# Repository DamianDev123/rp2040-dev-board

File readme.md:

# My RP2040 Dev Board

A simple RP2040 development board designed to help me learn PCB design and gain experience creating custom hardware.

## Features
- RP2040 microcontroller
- USB-C for power and programming
- BOOT and RESET buttons
- Status LED
- Broken out GPIO pins
- SWD debugging header
- Designed in KiCad

## Renders

### Front

### Back

## Project Structure

```
PCB/         - KiCad project files
Renders/     - PCB renders
Fabrication/ - Final Stuff
CAD/         - Just an export of the PCB
```

## Goals

This project was made to:
- Learn the PCB design workflow
- Practice schematic capture and PCB layout
- Understand RP2040 hardware design
- Gain experience preparing boards for manufacturing

## Software

Designed using **KiCad**.

## License

This project is open source under the MIT License.

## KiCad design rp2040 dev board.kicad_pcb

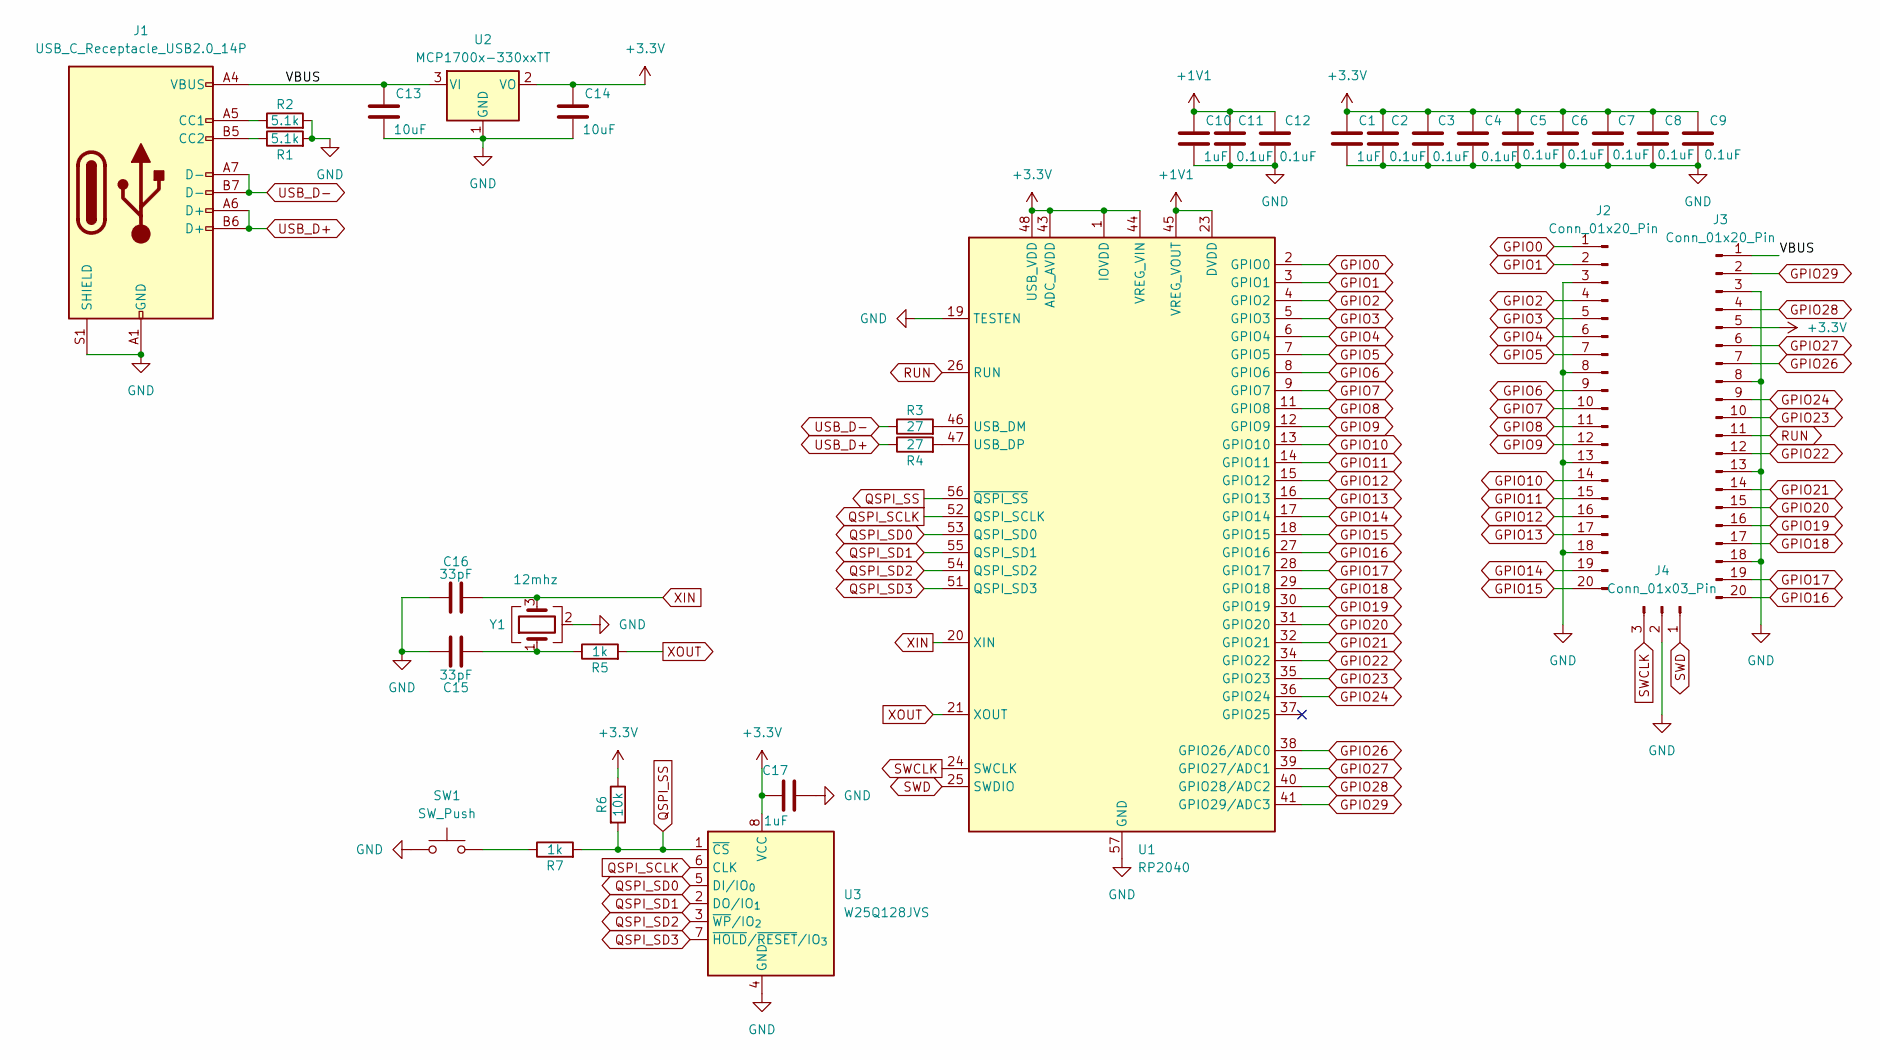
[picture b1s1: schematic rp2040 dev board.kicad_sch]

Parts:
C1, C10, C17: 1uF; C_0402_1005Metric
C2, C3, C4, C5, C6, C7, C8, C9, C11, C12: 0.1uF; C_0402_1005Metric
C13, C14: 10uF; C_0603_1608Metric
C15, C16: 33pF; C_0402_1005Metric
J1: USB_C_Receptacle_USB2.0_14P; USB_C_Receptacle_HRO_TYPE-C-31-M-12
J2, J3: Conn_01x20_Pin; PinHeader_1x20_P2.54mm_Vertical
J4: Conn_01x03_Pin; PinHeader_1x03_P2.54mm_Vertical
R1, R2: 5.1k; R_0402_1005Metric
R3, R4: 27; R_0402_1005Metric
R5, R7: 1k; R_0402_1005Metric
R6: 10k; R_0402_1005Metric
SW1: SW_Push; SW_Push_SPST_NO_Alps_SKRK
U1: RP2040; QFN-56-1EP_7x7mm_P0.4mm_EP3.2x3.2mm
U2: MCP1700x-330xxTT; SOT-23
U3: W25Q128JVS; Winbond_USON-8-1EP_3x2mm_P0.5mm_EP0.2x1.6mm
Y1: 12mhz; Crystal_SMD_3225-4Pin_3.2x2.5mm

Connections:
+1V1: C10.1, C11.1, C12.1, U1.23 (DVDD), U1.45 (VREG_VOUT), U1.50 (DVDD)
+3.3V: C1.1, C2.1, C3.1, C4.1, C5.1, C6.1, C7.1, C8.1, C9.1, C14.1, C17.1, J3.5, R6.1, U1.1 (IOVDD), U1.10 (IOVDD), U1.22 (IOVDD), U1.33 (IOVDD), U1.42 (IOVDD), U1.43 (ADC_AVDD), U1.44 (VREG_VIN), U1.48 (USB_VDD), U1.49 (IOVDD), U2.2 (VO), U3.8 (VCC)
/VBUS: C13.1, J1.A4 (VBUS), J1.A9 (VBUS), J1.B4 (VBUS), J1.B9 (VBUS), J3.1, U2.3 (VI)
GND: C1.2, C2.2, C3.2, C4.2, C5.2, C6.2, C7.2, C8.2, C9.2, C10.2, C11.2, C12.2, C13.2, C14.2, C15.1, C16.1, C17.2, J1.A1 (GND), J1.A12 (GND), J1.B1 (GND), J1.B12 (GND), J1.S1 (SHIELD), J2.3, J2.8, J2.13, J2.18, J3.3, J3.8, J3.13, J3.18, J4.2, R1.2, R2.2, SW1.1, U1.19 (TESTEN), U1.57 (GND), U2.1 (GND), U3.4 (GND), Y1.2 (G), Y1.4 (G)
GPIO0: J2.1, U1.2 (GPIO0)
GPIO1: J2.2, U1.3 (GPIO1)
GPIO2: J2.4, U1.4 (GPIO2)
GPIO3: J2.5, U1.5 (GPIO3)
GPIO4: J2.6, U1.6 (GPIO4)
GPIO5: J2.7, U1.7 (GPIO5)
GPIO6: J2.9, U1.8 (GPIO6)
GPIO7: J2.10, U1.9 (GPIO7)
GPIO8: J2.11, U1.11 (GPIO8)
GPIO9: J2.12, U1.12 (GPIO9)
GPIO10: J2.14, U1.13 (GPIO10)
GPIO11: J2.15, U1.14 (GPIO11)
GPIO12: J2.16, U1.15 (GPIO12)
GPIO13: J2.17, U1.16 (GPIO13)
GPIO14: J2.19, U1.17 (GPIO14)
GPIO15: J2.20, U1.18 (GPIO15)
GPIO16: J3.20, U1.27 (GPIO16)
GPIO17: J3.19, U1.28 (GPIO17)
GPIO18: J3.17, U1.29 (GPIO18)
GPIO19: J3.16, U1.30 (GPIO19)
GPIO20: J3.15, U1.31 (GPIO20)
GPIO21: J3.14, U1.32 (GPIO21)
GPIO22: J3.12, U1.34 (GPIO22)
GPIO23: J3.10, U1.35 (GPIO23)
GPIO24: J3.9, U1.36 (GPIO24)
GPIO26: J3.7, U1.38 (GPIO26/ADC0)
GPIO27: J3.6, U1.39 (GPIO27/ADC1)
GPIO28: J3.4, U1.40 (GPIO28/ADC2)
GPIO29: J3.2, U1.41 (GPIO29/ADC3)
unnamed: C15.2, R5.1, Y1.1
unnamed: J1.A5 (CC1), R2.1
unnamed: J1.B5 (CC2), R1.1
unnamed: R7.1, SW1.2
unnamed: R3.2, U1.46 (USB_DM)
unnamed: R4.2, U1.47 (USB_DP)
QSPI_SCLK: U1.52 (QSPI_SCLK), U3.6 (CLK)
QSPI_SD0: U1.53 (QSPI_SD0), U3.5 (DI/IO_{0})
QSPI_SD1: U1.55 (QSPI_SD1), U3.2 (DO/IO_{1})
QSPI_SD2: U1.54 (QSPI_SD2), U3.3 (~WP/IO_{2})
QSPI_SD3: U1.51 (QSPI_SD3), U3.7 (~HOLD/~RESET/IO_{3})
QSPI_SS: R6.2, R7.2, U1.56 (~QSPI_SS), U3.1 (~CS)
RUN: J3.11, U1.26 (RUN)
SWCLK: J4.3, U1.24 (SWCLK)
SWD: J4.1, U1.25 (SWDIO)
USB_D+: J1.A6 (D+), J1.B6 (D+), R4.1
USB_D-: J1.A7 (D-), J1.B7 (D-), R3.1
XIN: C16.2, U1.20 (XIN), Y1.3
XOUT: R5.2, U1.21 (XOUT)

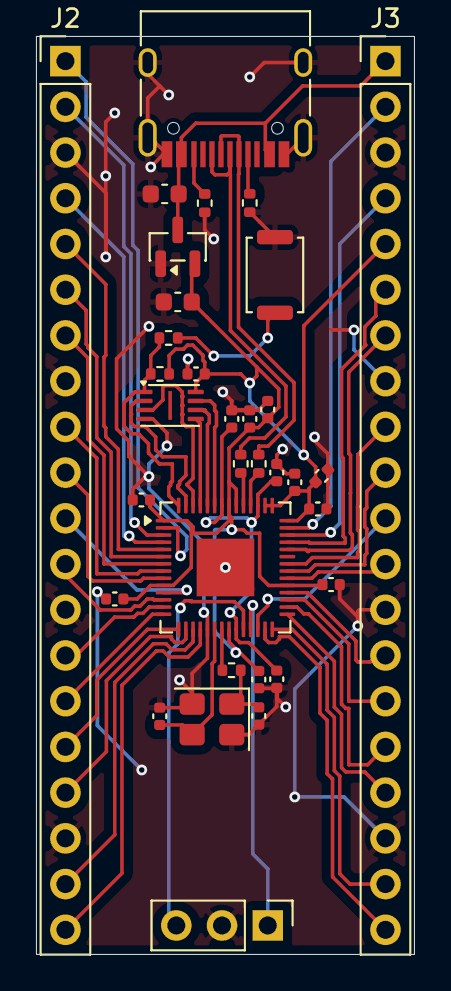
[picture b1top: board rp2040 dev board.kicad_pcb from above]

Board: 2 copper layers, 21.0 x 51.0 mm, 33 parts (0 on the bottom side), 52 nets.

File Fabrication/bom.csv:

Designator,Footprint,Quantity,Value,LCSC Part #
"C1, C10, C17",0402,3,1uF,
"C11, C12, C2, C3, C4, C5, C6, C7, C8, C9",0402,10,0.1uF,
"C13, C14",0603,2,10uF,
"C15, C16",0402,2,33pF,
J1,USB_C_Receptacle_HRO_TYPE-C-31-M-12,1,USB_C_Receptacle_USB2.0_14P,
"J2, J3",PinHeader_1x20_P2.54mm_Vertical,2,Conn_01x20_Pin,
J4,PinHeader_1x03_P2.54mm_Vertical,1,Conn_01x03_Pin,
"R1, R2",0402,2,5.1k,
"R3, R4",0402,2,27,
"R5, R7",0402,2,1k,
R6,0402,1,10k,
SW1,SW_Push_SPST_NO_Alps_SKRK,1,SW_Push,
U1,QFN-56-1EP_7x7mm_P0.4mm_EP3.2x3.2mm,1,RP2040,
U2,SOT-23,1,MCP1700x-330xxTT,
U3,Winbond_USON-8-1EP_3x2mm_P0.5mm_EP0.2x1.6mm,1,W25Q128JVS,
Y1,Crystal_SMD_3225-4Pin_3.2x2.5mm,1,12mhz,
